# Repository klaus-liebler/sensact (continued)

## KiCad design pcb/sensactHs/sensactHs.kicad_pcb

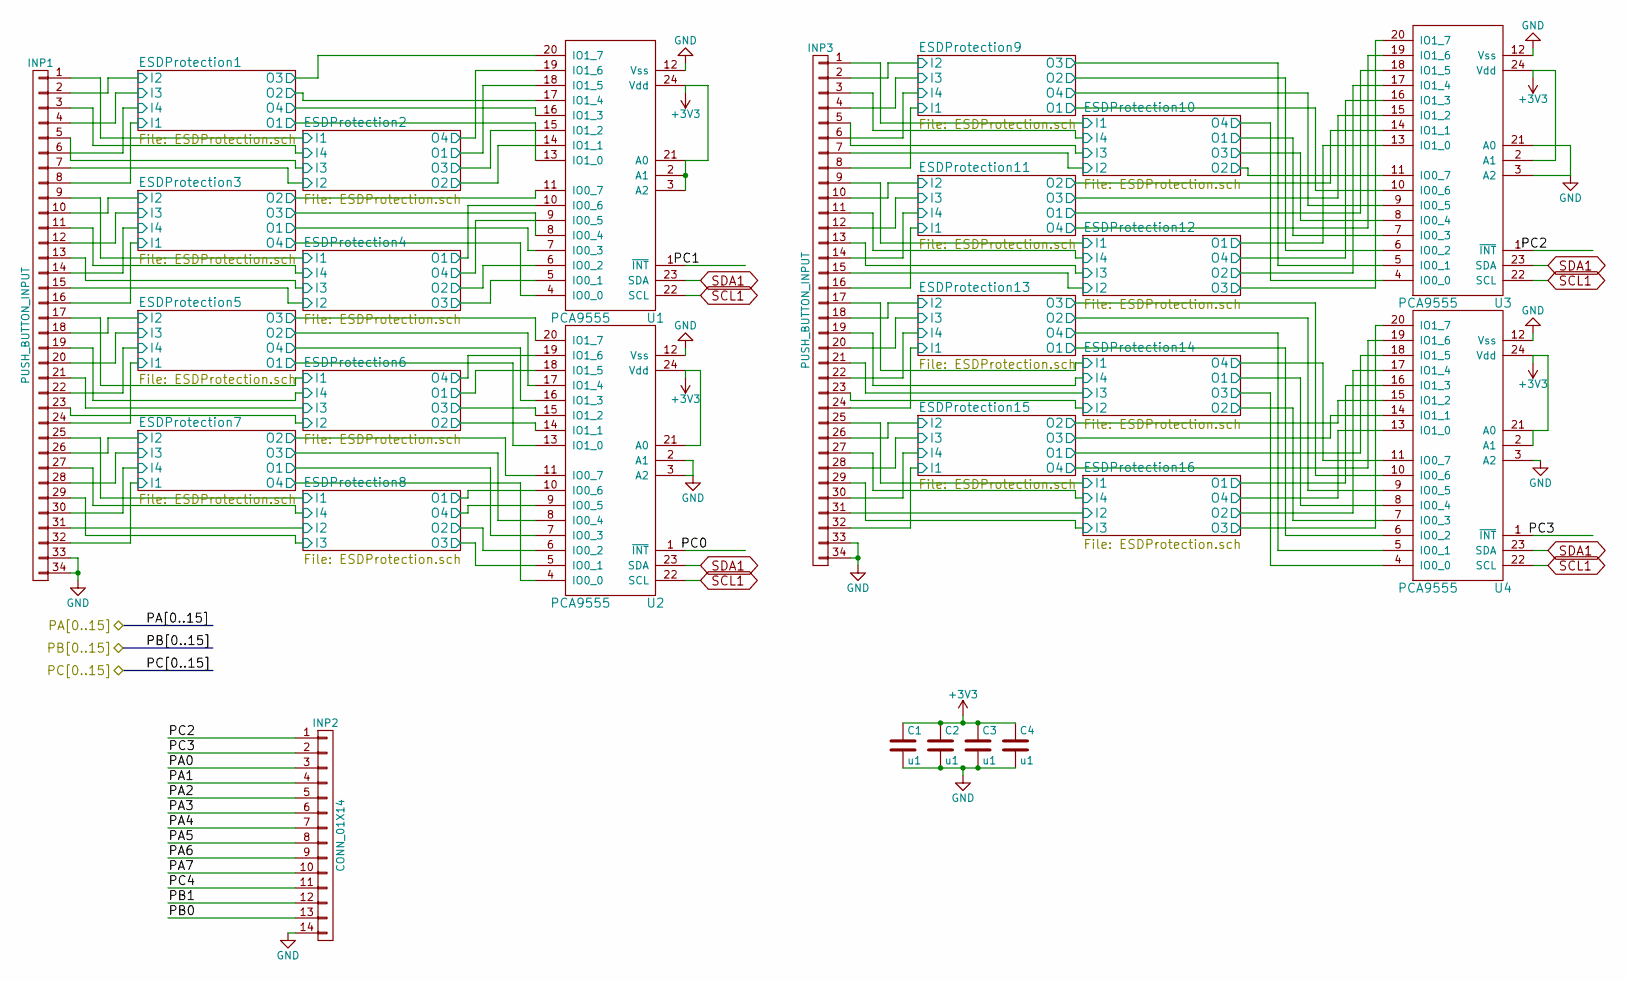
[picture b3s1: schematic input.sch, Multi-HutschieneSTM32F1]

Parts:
C1, C2, C3, C4: u1; C_0805_HandSoldering
INP1, INP3: PUSH_BUTTON_INPUT; vasch_strip_17x2
INP2: CONN_01X14; vasch_strip_7x2
U1, U2, U3, U4: PCA9555; TSSOP-24_4.4x7.8mm_Pitch0.65mm_handsolder

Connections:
/01 input/ESDProtection1/I1: INP1.8; also elsewhere on the board
/01 input/ESDProtection1/I2: INP1.2; also elsewhere on the board
/01 input/ESDProtection1/I3: INP1.4; also elsewhere on the board
/01 input/ESDProtection1/I4: INP1.6; also elsewhere on the board
/01 input/ESDProtection1/O1: U1.13 (IO1_0); also elsewhere on the board
/01 input/ESDProtection1/O2: U1.17 (IO1_4); also elsewhere on the board
/01 input/ESDProtection1/O3: U1.20 (IO1_7); also elsewhere on the board
/01 input/ESDProtection1/O4: U1.16 (IO1_3); also elsewhere on the board
/01 input/ESDProtection2/I1: INP1.1; also elsewhere on the board
/01 input/ESDProtection2/I2: INP1.7; also elsewhere on the board
/01 input/ESDProtection2/I3: INP1.5; also elsewhere on the board
/01 input/ESDProtection2/I4: INP1.3; also elsewhere on the board
/01 input/ESDProtection2/O1: U1.18 (IO1_5); also elsewhere on the board
/01 input/ESDProtection2/O2: U1.14 (IO1_1); also elsewhere on the board
/01 input/ESDProtection2/O3: U1.15 (IO1_2); also elsewhere on the board
/01 input/ESDProtection2/O4: U1.19 (IO1_6); also elsewhere on the board
/01 input/ESDProtection3/I1: INP1.16; also elsewhere on the board
/01 input/ESDProtection3/I2: INP1.10; also elsewhere on the board
/01 input/ESDProtection3/I3: INP1.12; also elsewhere on the board
/01 input/ESDProtection3/I4: INP1.14; also elsewhere on the board
/01 input/ESDProtection3/O1: U1.7 (IO0_3); also elsewhere on the board
/01 input/ESDProtection3/O2: U1.11 (IO0_7); also elsewhere on the board
/01 input/ESDProtection3/O3: U1.8 (IO0_4); also elsewhere on the board
/01 input/ESDProtection3/O4: U1.4 (IO0_0); also elsewhere on the board
/01 input/ESDProtection4/I1: INP1.9; also elsewhere on the board
/01 input/ESDProtection4/I2: INP1.15; also elsewhere on the board
/01 input/ESDProtection4/I3: INP1.13; also elsewhere on the board
/01 input/ESDProtection4/I4: INP1.11; also elsewhere on the board
/01 input/ESDProtection4/O1: U1.10 (IO0_6); also elsewhere on the board
/01 input/ESDProtection4/O2: U1.6 (IO0_2); also elsewhere on the board
/01 input/ESDProtection4/O3: U1.5 (IO0_1); also elsewhere on the board
/01 input/ESDProtection4/O4: U1.9 (IO0_5); also elsewhere on the board
/01 input/ESDProtection5/I1: INP1.24; also elsewhere on the board
/01 input/ESDProtection5/I2: INP1.18; also elsewhere on the board
/01 input/ESDProtection5/I3: INP1.20; also elsewhere on the board
/01 input/ESDProtection5/I4: INP1.22; also elsewhere on the board
/01 input/ESDProtection5/O1: U2.13 (IO1_0); also elsewhere on the board
/01 input/ESDProtection5/O2: U2.17 (IO1_4); also elsewhere on the board
/01 input/ESDProtection5/O3: U2.20 (IO1_7); also elsewhere on the board
/01 input/ESDProtection5/O4: U2.16 (IO1_3); also elsewhere on the board
/01 input/ESDProtection6/I1: INP1.17; also elsewhere on the board
/01 input/ESDProtection6/I2: INP1.23; also elsewhere on the board
/01 input/ESDProtection6/I3: INP1.21; also elsewhere on the board
/01 input/ESDProtection6/I4: INP1.19; also elsewhere on the board
/01 input/ESDProtection6/O1: U2.18 (IO1_5); also elsewhere on the board
/01 input/ESDProtection6/O2: U2.14 (IO1_1); also elsewhere on the board
/01 input/ESDProtection6/O3: U2.15 (IO1_2); also elsewhere on the board
/01 input/ESDProtection6/O4: U2.19 (IO1_6); also elsewhere on the board
/01 input/ESDProtection7/I1: INP1.32; also elsewhere on the board
/01 input/ESDProtection7/I2: INP1.26; also elsewhere on the board
/01 input/ESDProtection7/I3: INP1.28; also elsewhere on the board
/01 input/ESDProtection7/I4: INP1.30; also elsewhere on the board
/01 input/ESDProtection7/O1: U2.7 (IO0_3); also elsewhere on the board
/01 input/ESDProtection7/O2: U2.11 (IO0_7); also elsewhere on the board
/01 input/ESDProtection7/O3: U2.8 (IO0_4); also elsewhere on the board
/01 input/ESDProtection7/O4: U2.4 (IO0_0); also elsewhere on the board
/01 input/ESDProtection8/I1: INP1.25; also elsewhere on the board
/01 input/ESDProtection8/I2: INP1.31; also elsewhere on the board
/01 input/ESDProtection8/I3: INP1.29; also elsewhere on the board
/01 input/ESDProtection8/I4: INP1.27; also elsewhere on the board
/01 input/ESDProtection8/O1: U2.10 (IO0_6); also elsewhere on the board
/01 input/ESDProtection8/O2: U2.6 (IO0_2); also elsewhere on the board
/01 input/ESDProtection8/O3: U2.5 (IO0_1); also elsewhere on the board
/01 input/ESDProtection8/O4: U2.9 (IO0_5); also elsewhere on the board
/01 input/ESDProtection9/I1: INP3.8; also elsewhere on the board
/01 input/ESDProtection9/I2: INP3.2; also elsewhere on the board
/01 input/ESDProtection9/I3: INP3.4; also elsewhere on the board
/01 input/ESDProtection9/I4: INP3.6; also elsewhere on the board
/01 input/ESDProtection9/O1: U3.10 (IO0_6); also elsewhere on the board
/01 input/ESDProtection9/O2: U3.6 (IO0_2); also elsewhere on the board
/01 input/ESDProtection9/O3: U3.5 (IO0_1); also elsewhere on the board
/01 input/ESDProtection9/O4: U3.9 (IO0_5); also elsewhere on the board
/01 input/ESDProtection10/I1: INP3.1; also elsewhere on the board
/01 input/ESDProtection10/I2: INP3.7; also elsewhere on the board
/01 input/ESDProtection10/I3: INP3.5; also elsewhere on the board
/01 input/ESDProtection10/I4: INP3.3; also elsewhere on the board
/01 input/ESDProtection10/O1: U3.7 (IO0_3); also elsewhere on the board
/01 input/ESDProtection10/O2: U3.11 (IO0_7); also elsewhere on the board
/01 input/ESDProtection10/O3: U3.8 (IO0_4); also elsewhere on the board
/01 input/ESDProtection10/O4: U3.4 (IO0_0); also elsewhere on the board
/01 input/ESDProtection11/I1: INP3.16; also elsewhere on the board
/01 input/ESDProtection11/I2: INP3.10; also elsewhere on the board
/01 input/ESDProtection11/I3: INP3.12; also elsewhere on the board
/01 input/ESDProtection11/I4: INP3.14; also elsewhere on the board
/01 input/ESDProtection11/O1: U3.18 (IO1_5); also elsewhere on the board
/01 input/ESDProtection11/O2: U3.14 (IO1_1); also elsewhere on the board
/01 input/ESDProtection11/O3: U3.15 (IO1_2); also elsewhere on the board
/01 input/ESDProtection11/O4: U3.19 (IO1_6); also elsewhere on the board
/01 input/ESDProtection12/I1: INP3.9; also elsewhere on the board
/01 input/ESDProtection12/I2: INP3.15; also elsewhere on the board
/01 input/ESDProtection12/I3: INP3.13; also elsewhere on the board
/01 input/ESDProtection12/I4: INP3.11; also elsewhere on the board
/01 input/ESDProtection12/O1: U3.13 (IO1_0); also elsewhere on the board
/01 input/ESDProtection12/O2: U3.17 (IO1_4); also elsewhere on the board
/01 input/ESDProtection12/O3: U3.20 (IO1_7); also elsewhere on the board
/01 input/ESDProtection12/O4: U3.16 (IO1_3); also elsewhere on the board
/01 input/ESDProtection13/I1: INP3.24; also elsewhere on the board
/01 input/ESDProtection13/I2: INP3.18; also elsewhere on the board
/01 input/ESDProtection13/I3: INP3.20; also elsewhere on the board
/01 input/ESDProtection13/I4: INP3.22; also elsewhere on the board
/01 input/ESDProtection13/O1: U4.6 (IO0_2); also elsewhere on the board
/01 input/ESDProtection13/O2: U4.9 (IO0_5); also elsewhere on the board
/01 input/ESDProtection13/O3: U4.10 (IO0_6); also elsewhere on the board
/01 input/ESDProtection13/O4: U4.5 (IO0_1); also elsewhere on the board
/01 input/ESDProtection14/I1: INP3.17; also elsewhere on the board
/01 input/ESDProtection14/I2: INP3.23; also elsewhere on the board
/01 input/ESDProtection14/I3: INP3.21; also elsewhere on the board
/01 input/ESDProtection14/I4: INP3.19; also elsewhere on the board
/01 input/ESDProtection14/O1: U4.8 (IO0_4); also elsewhere on the board
/01 input/ESDProtection14/O2: U4.7 (IO0_3); also elsewhere on the board
/01 input/ESDProtection14/O3: U4.4 (IO0_0); also elsewhere on the board
/01 input/ESDProtection14/O4: U4.11 (IO0_7); also elsewhere on the board
/01 input/ESDProtection15/I1: INP3.32; also elsewhere on the board
/01 input/ESDProtection15/I2: INP3.26; also elsewhere on the board
/01 input/ESDProtection15/I3: INP3.28; also elsewhere on the board
/01 input/ESDProtection15/I4: INP3.30; also elsewhere on the board
/01 input/ESDProtection15/O1: U4.18 (IO1_5); also elsewhere on the board
/01 input/ESDProtection15/O2: U4.15 (IO1_2); also elsewhere on the board
/01 input/ESDProtection15/O3: U4.14 (IO1_1); also elsewhere on the board
/01 input/ESDProtection15/O4: U4.19 (IO1_6); also elsewhere on the board
/01 input/ESDProtection16/I1: INP3.25; also elsewhere on the board
/01 input/ESDProtection16/I2: INP3.31; also elsewhere on the board
/01 input/ESDProtection16/I3: INP3.29; also elsewhere on the board
/01 input/ESDProtection16/I4: INP3.27; also elsewhere on the board
/01 input/ESDProtection16/O1: U4.16 (IO1_3); also elsewhere on the board
/01 input/ESDProtection16/O2: U4.17 (IO1_4); also elsewhere on the board
/01 input/ESDProtection16/O3: U4.20 (IO1_7); also elsewhere on the board
/01 input/ESDProtection16/O4: U4.13 (IO1_0); also elsewhere on the board
/01 input/PA0: INP2.3; also elsewhere on the board
/01 input/PA1: INP2.4; also elsewhere on the board
/01 input/PA2: INP2.5; also elsewhere on the board
/01 input/PA3: INP2.13; also elsewhere on the board
/01 input/PA4: INP2.11; also elsewhere on the board
/01 input/PA5: INP2.12; also elsewhere on the board
/01 input/PA6: INP2.9; also elsewhere on the board
/01 input/PA7: INP2.10; also elsewhere on the board
/01 input/PB0: INP2.8; also elsewhere on the board
/01 input/PC0: U2.1 (~INT); also elsewhere on the board
/01 input/PC1: U1.1 (~INT); also elsewhere on the board
/01 input/PC4: INP2.7; also elsewhere on the board
/PB1: INP2.6; also elsewhere on the board
GND: C1.2, C2.2, C3.2, C4.2, INP1.33, INP1.34, INP2.14, INP3.33, INP3.34, U1.12 (Vss), U2.2 (A1), U2.3 (A2), U2.12 (Vss), U3.3 (A2), U3.12 (Vss), U3.21 (A0), U4.3 (A2), U4.12 (Vss); also elsewhere on the board
SCL1: U1.22 (SCL), U2.22 (SCL), U3.22 (SCL), U4.22 (SCL); also elsewhere on the board
SDA1: U1.23 (SDA), U2.23 (SDA), U3.23 (SDA), U4.23 (SDA); also elsewhere on the board

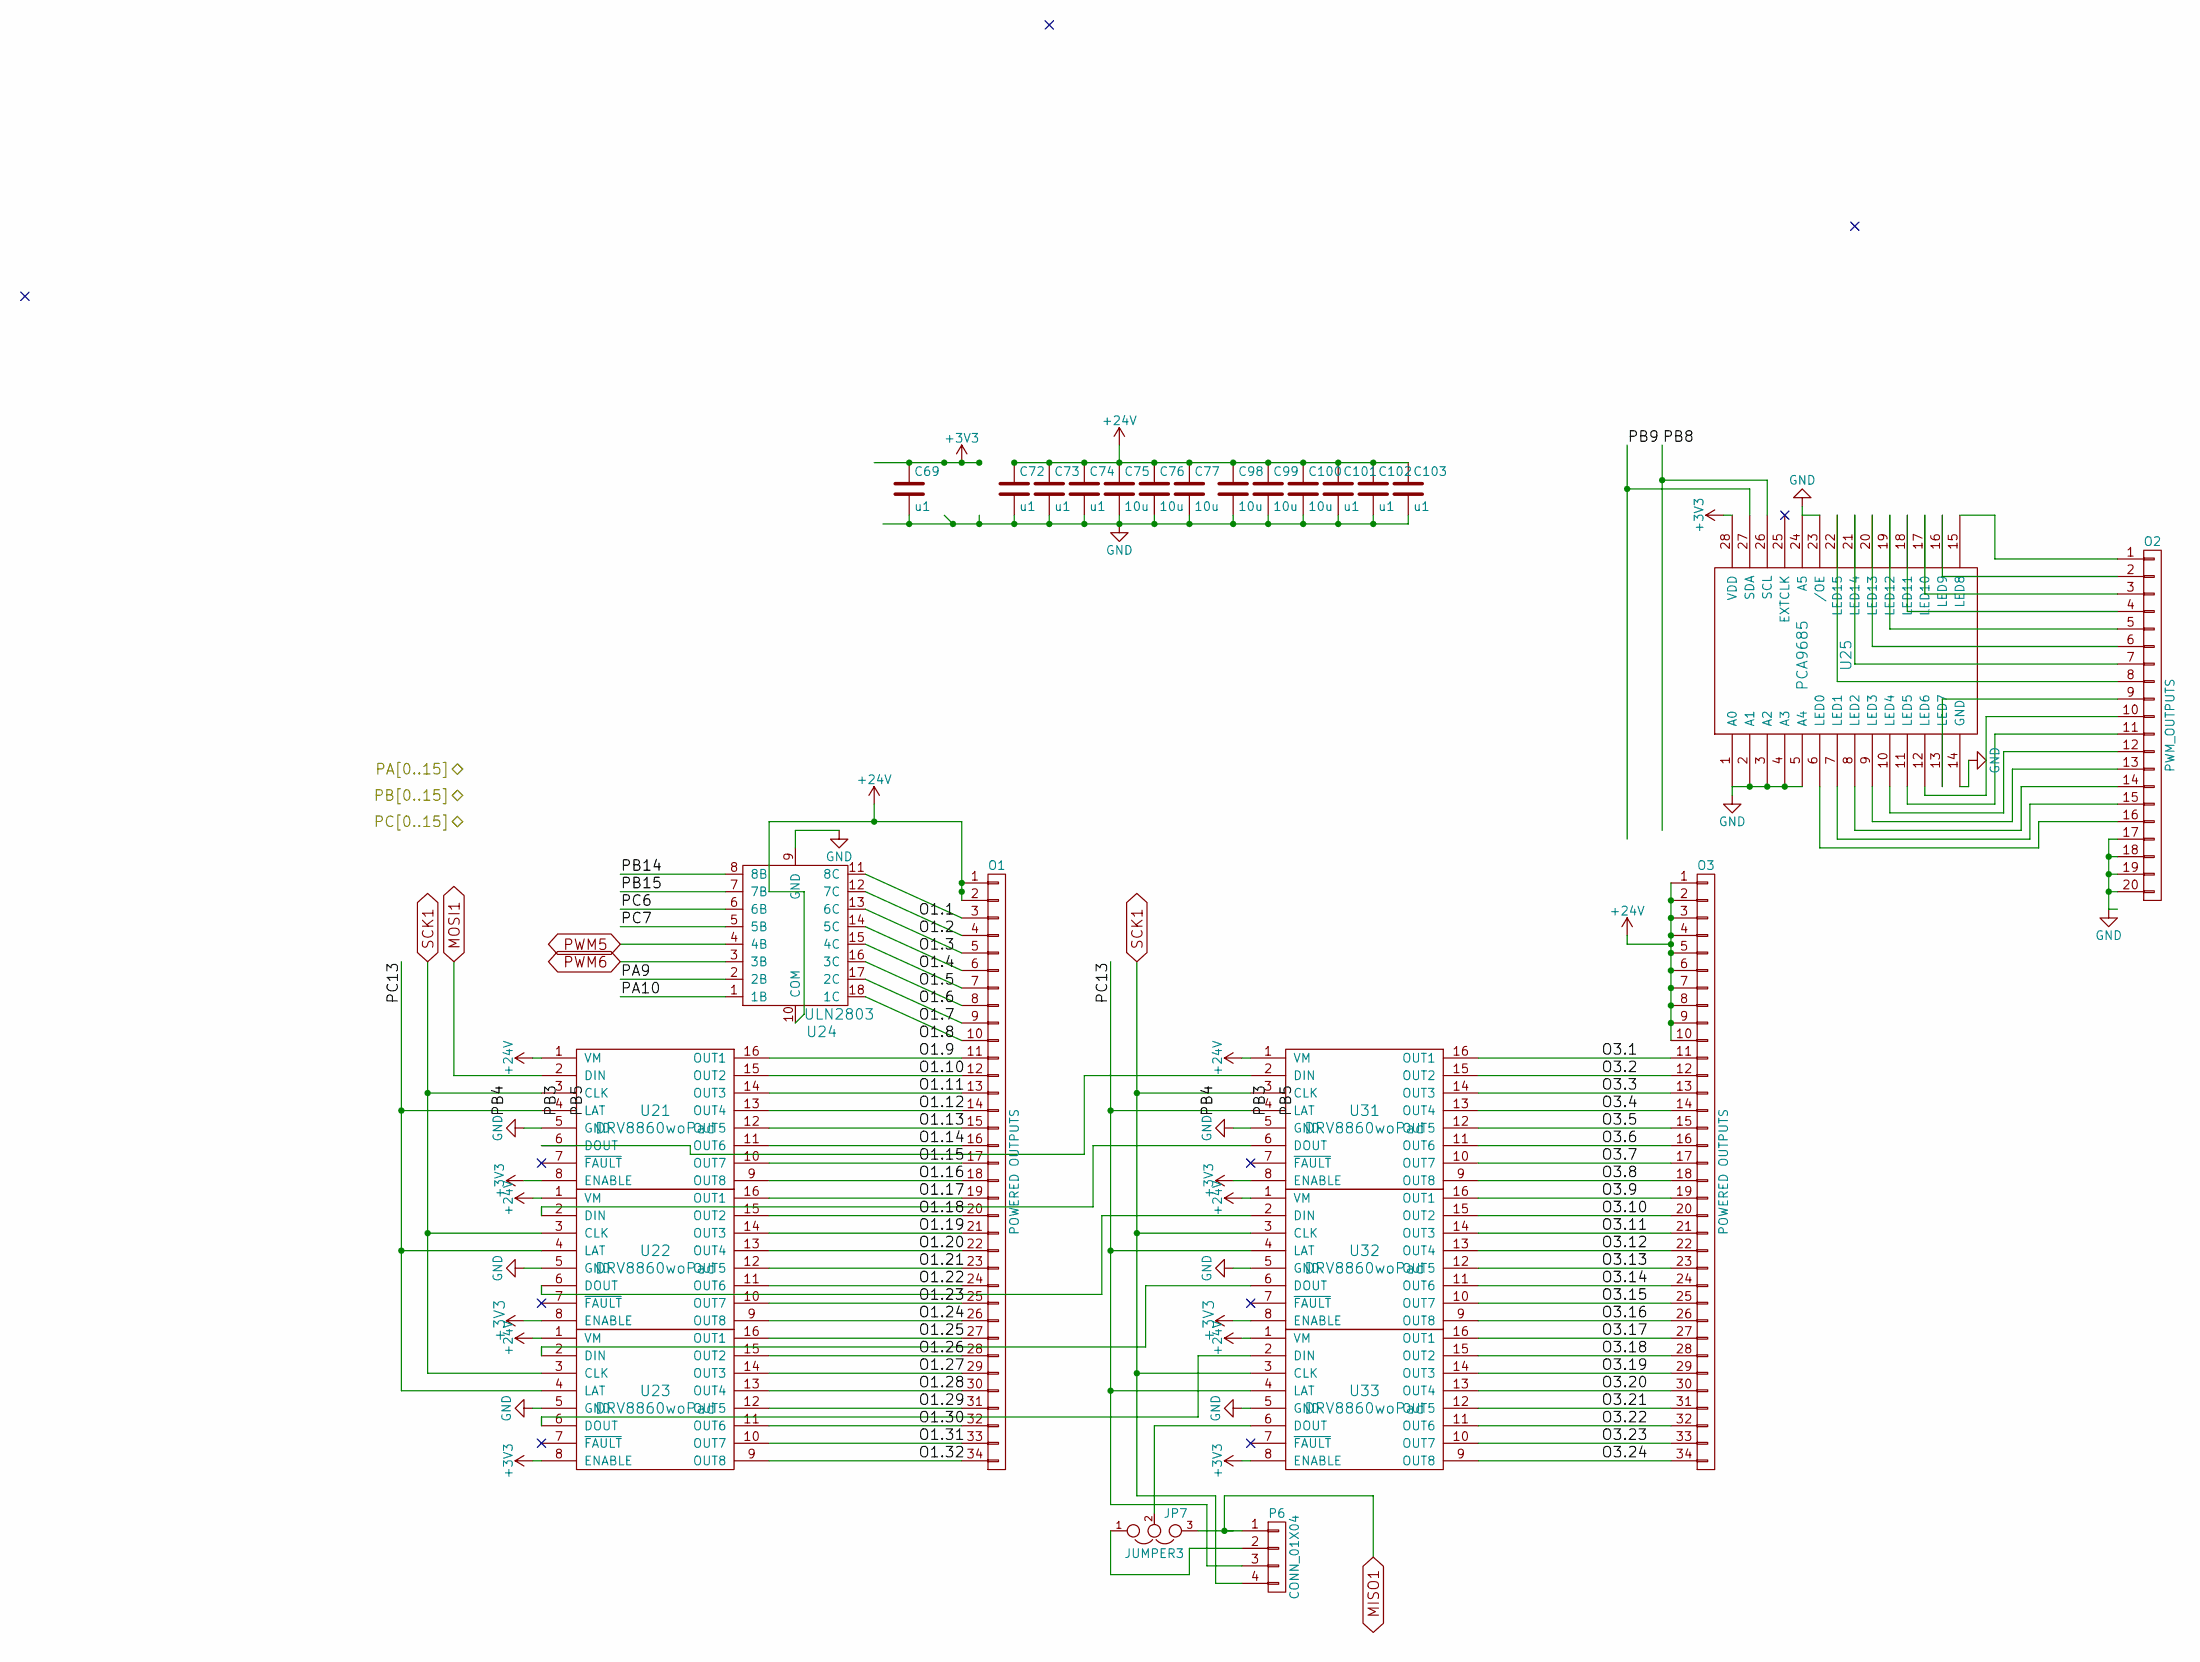
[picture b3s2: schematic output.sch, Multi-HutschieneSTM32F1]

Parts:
C69, C72, C73, C74, C101, C102, C103: u1; C_0805_HandSoldering
C75, C76, C77, C98, C99, C100: 10u; C_1206_HandSoldering
JP7: JUMPER3; SMD-solder-bridge-3pin
O1, O3: POWERED OUTPUTS; vasch_strip_17x2
O2: PWM_OUTPUTS; vasch_strip_10x2
P6: CONN_01X04; Pin_Header_Straight_2x02
U21, U22, U23, U31, U32, U33: DRV8860woPad; TSSOP-16_4.4x5mm_Pitch0.65mm_handsolder
U24: ULN2803; SOIC-18_7.5x11.6mm_Pitch1.27mm_handsolder
U25: PCA9685; TSSOP-28_4.4x9.7mm_Pitch0.65mm_handsolder

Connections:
+24V: C72.1, C73.1, C74.1, C75.1, C76.1, C77.1, C98.1, C99.1, C100.1, C101.1, C102.1, C103.1, O1.1, O1.2, O3.1, O3.2, O3.3, O3.4, O3.5, O3.6, O3.7, O3.8, O3.9, O3.10, U21.1 (VM), U22.1 (VM), U23.1 (VM), U24.10 (COM), U31.1 (VM), U32.1 (VM), U33.1 (VM); also elsewhere on the board
/02 output/O1.9: O1.11, U21.16 (OUT1)
/02 output/O1.10: O1.12, U21.15 (OUT2)
/02 output/O1.11: O1.13, U21.14 (OUT3)
/02 output/O1.12: O1.14, U21.13 (OUT4)
/02 output/O1.13: O1.15, U21.12 (OUT5)
/02 output/O1.14: O1.16, U21.11 (OUT6)
/02 output/O1.15: O1.17, U21.10 (OUT7)
/02 output/O1.16: O1.18, U21.9 (OUT8)
/02 output/O1.17: O1.19, U22.16 (OUT1)
/02 output/O1.18: O1.20, U22.15 (OUT2)
/02 output/O1.19: O1.21, U22.14 (OUT3)
/02 output/O1.20: O1.22, U22.13 (OUT4)
/02 output/O1.21: O1.23, U22.12 (OUT5)
/02 output/O1.22: O1.24, U22.11 (OUT6)
/02 output/O1.23: O1.25, U22.10 (OUT7)
/02 output/O1.24: O1.26, U22.9 (OUT8)
/02 output/O1.25: O1.27, U23.16 (OUT1)
/02 output/O1.26: O1.28, U23.15 (OUT2)
/02 output/O1.27: O1.29, U23.14 (OUT3)
/02 output/O1.28: O1.30, U23.13 (OUT4)
/02 output/O1.29: O1.31, U23.12 (OUT5)
/02 output/O1.30: O1.32, U23.11 (OUT6)
/02 output/O1.31: O1.33, U23.10 (OUT7)
/02 output/O1.32: O1.34, U23.9 (OUT8)
/02 output/O3.1: O3.11, U31.16 (OUT1)
/02 output/O3.2: O3.12, U31.15 (OUT2)
/02 output/O3.3: O3.13, U31.14 (OUT3)
/02 output/O3.4: O3.14, U31.13 (OUT4)
/02 output/O3.5: O3.15, U31.12 (OUT5)
/02 output/O3.6: O3.16, U31.11 (OUT6)
/02 output/O3.7: O3.17, U31.10 (OUT7)
/02 output/O3.8: O3.18, U31.9 (OUT8)
/02 output/O3.9: O3.19, U32.16 (OUT1)
/02 output/O3.10: O3.20, U32.15 (OUT2)
/02 output/O3.11: O3.21, U32.14 (OUT3)
/02 output/O3.12: O3.22, U32.13 (OUT4)
/02 output/O3.13: O3.23, U32.12 (OUT5)
/02 output/O3.14: O3.24, U32.11 (OUT6)
/02 output/O3.15: O3.25, U32.10 (OUT7)
/02 output/O3.16: O3.26, U32.9 (OUT8)
/02 output/O3.17: O3.27, U33.16 (OUT1)
/02 output/O3.18: O3.28, U33.15 (OUT2)
/02 output/O3.19: O3.29, U33.14 (OUT3)
/02 output/O3.20: O3.30, U33.13 (OUT4)
/02 output/O3.21: O3.31, U33.12 (OUT5)
/02 output/O3.22: O3.32, U33.11 (OUT6)
/02 output/O3.23: O3.33, U33.10 (OUT7)
/02 output/O3.24: O3.34, U33.9 (OUT8)
/02 output/PA9: U24.2 (2B); also elsewhere on the board
/02 output/PA10: U24.1 (1B); also elsewhere on the board
/02 output/PB14: U24.8 (8B); also elsewhere on the board
/02 output/PB15: U24.7 (7B); also elsewhere on the board
/02 output/PC6: U24.6 (6B); also elsewhere on the board
/02 output/PC7: U24.5 (5B); also elsewhere on the board
GND: C69.2, C72.2, C73.2, C74.2, C75.2, C76.2, C77.2, C98.2, C99.2, C100.2, C101.2, C102.2, C103.2, O2.17, O2.18, O2.19, O2.20, U21.5 (GND), U22.5 (GND), U23.5 (GND), U24.9 (GND), U25.1 (A0), U25.2 (A1), U25.3 (A2), U25.4 (A3), U25.5 (A4), U25.14 (GND), U25.23 (/OE), U25.24 (A5), U31.5 (GND), U32.5 (GND), U33.5 (GND); also elsewhere on the board
MOSI1: U21.2 (DIN); also elsewhere on the board
unnamed: O1.3, U24.11 (8C)
unnamed: O1.4, U24.12 (7C)
unnamed: O1.5, U24.13 (6C)
unnamed: O1.6, U24.14 (5C)
unnamed: O1.7, U24.15 (4C)
unnamed: O1.8, U24.16 (3C)
unnamed: O1.9, U24.17 (2C)
unnamed: O1.10, U24.18 (1C)
unnamed: O2.1, U25.15 (LED8)
unnamed: O2.2, U25.16 (LED9)
unnamed: O2.3, U25.17 (LED10)
unnamed: O2.4, U25.18 (LED11)
unnamed: O2.5, U25.19 (LED12)
unnamed: O2.6, U25.20 (LED13)
unnamed: O2.7, U25.21 (LED14)
unnamed: O2.8, U25.22 (LED15)
unnamed: O2.9, U25.13 (LED7)
unnamed: O2.10, U25.12 (LED6)
unnamed: O2.11, U25.11 (LED5)
unnamed: O2.12, U25.10 (LED4)
unnamed: O2.13, U25.9 (LED3)
unnamed: O2.14, U25.8 (LED2)
unnamed: O2.15, U25.7 (LED1)
unnamed: O2.16, U25.6 (LED0)
unnamed: U21.6 (DOUT), U31.2 (DIN)
unnamed: U22.2 (DIN), U31.6 (DOUT)
unnamed: U22.6 (DOUT), U32.2 (DIN)
unnamed: U23.2 (DIN), U32.6 (DOUT)
unnamed: U23.6 (DOUT), U33.2 (DIN)
PWM5: U24.4 (4B); also elsewhere on the board
PWM6: U24.3 (3B); also elsewhere on the board
SCL1: U25.26 (SCL); also elsewhere on the board
SDA1: U25.27 (SDA); also elsewhere on the board

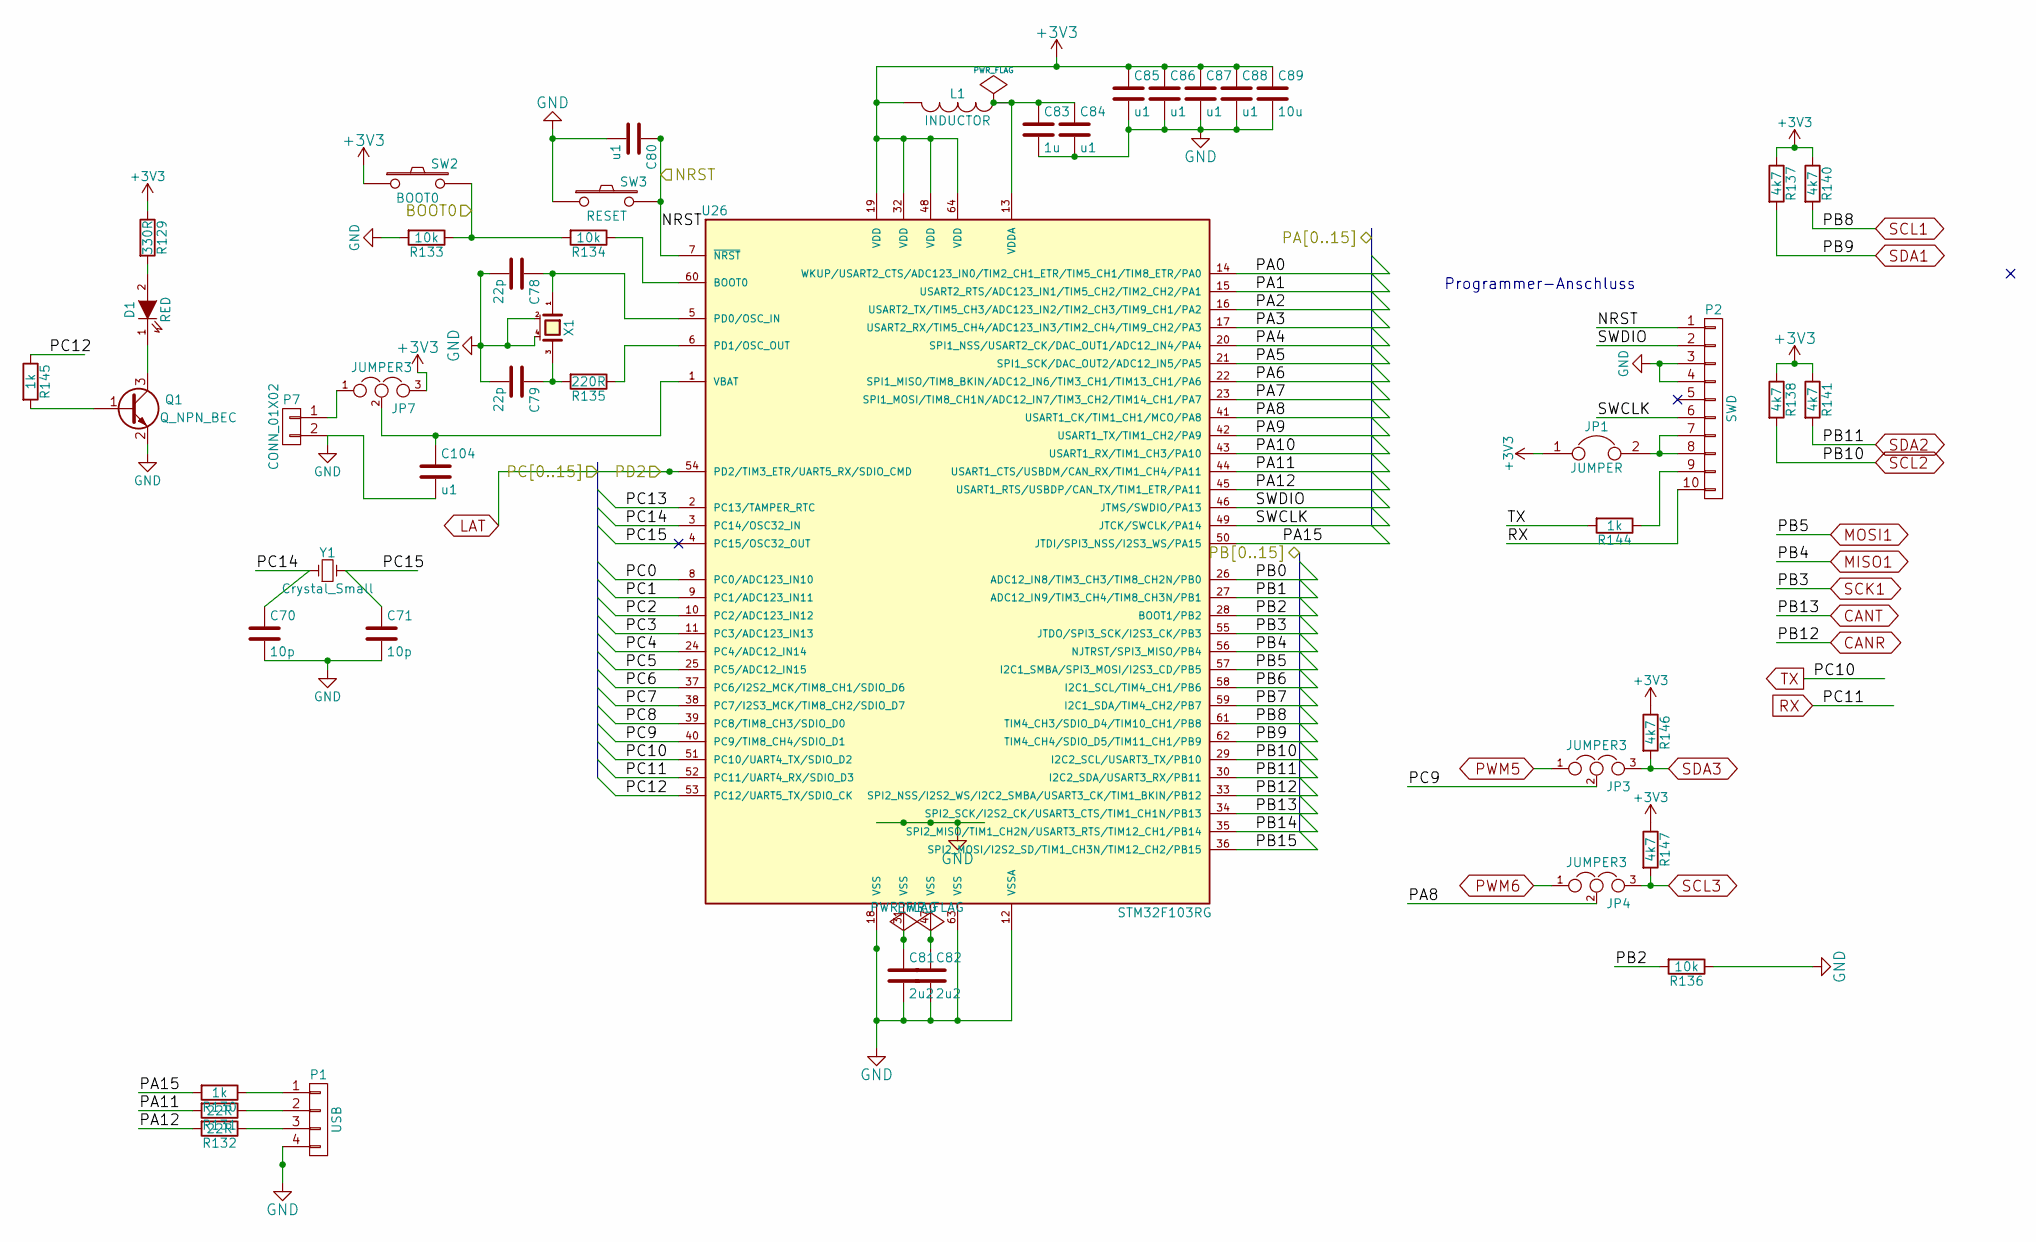
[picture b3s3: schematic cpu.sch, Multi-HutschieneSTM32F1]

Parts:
C70, C71: 10p; C_0805_HandSoldering
C78, C79: 22p; C_0805_HandSoldering
C80, C84, C85, C86, C87, C88, C104: u1; C_0805_HandSoldering
C81, C82: 2u2; C_0805_HandSoldering
C83: 1u; C_0805_HandSoldering
C89: 10u; C_1206_HandSoldering
D1: RED; LED_5730
JP1: JUMPER; Pin_Header_Straight_1x02
JP3, JP4, JP7: JUMPER3; SMD-solder-bridge-3pin
L1: INDUCTOR; R_1206_HandSoldering
P1: USB; Pin_Header_Straight_1x04
P2: SWD; vasch_strip_5x2
P7: CONN_01X02; Pin_Header_Straight_1x02
Q1: Q_NPN_BEC; SOT-23_Handsoldering
R129: 330R; R_1206_HandSoldering
R130, R144, R145: 1k; R_0805_HandSoldering
R131, R132: 22R; R_0805_HandSoldering
R133, R134, R136: 10k; R_0805_HandSoldering
R135: 220R; R_0805_HandSoldering
R137, R138, R140, R141, R146, R147: 4k7; R_0805_HandSoldering
SW2: BOOT0; SW_PUSH_SMALL
SW3: RESET; SW_PUSH_SMALL
U26: STM32F103RG; LQFP-64_10x10mm_Pitch0.5mm_handsolder
X1: CRYSTAL_SMD_4pol; quartz3225
Y1: Crystal_Small; Crystal_Watch

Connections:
/01 input/PA0: U26.14 (WKUP/USART2_CTS/ADC123_IN0/TIM2_CH1_ETR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); also elsewhere on the board
/01 input/PA1: U26.15 (USART2_RTS/ADC123_IN1/TIM5_CH2/TIM2_CH2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); also elsewhere on the board
/01 input/PA2: U26.16 (USART2_TX/TIM5_CH3/ADC123_IN2/TIM2_CH3/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); also elsewhere on the board
/01 input/PA3: U26.17 (USART2_RX/TIM5_CH4/ADC123_IN3/TIM2_CH4/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); also elsewhere on the board
/01 input/PA4: U26.20 (SPI1_NSS/USART2_CK/DAC_OUT1/ADC12_IN4/P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); also elsewhere on the board
/01 input/PA5: U26.21 (SPI1_SCK/DAC_OUT2/ADC12_IN5/PA5); also elsewhere on the board
/01 input/PA6: U26.22 (SPI1_MISO/TIM8_BKIN/ADC12_IN6/TIM3_CH1/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); also elsewhere on the board
/01 input/PA7: U26.23 (SPI1_MOSI/TIM8_CH1N/ADC12_IN7/TIM3_CH2/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); also elsewhere on the board
/01 input/PB0: U26.26 (ADC12_IN8/TIM3_CH3/TIM8_CH2N/PB0); also elsewhere on the board
/01 input/PC0: U26.8 (PC0/ADC123_IN10); also elsewhere on the board
/01 input/PC1: U26.9 (PC1/ADC123_IN11); also elsewhere on the board
/01 input/PC4: U26.24 (PC4/ADC12_IN14); also elsewhere on the board
/02 output/PA9: U26.42 (USART1_TX/TIM1_CH2/PA9); also elsewhere on the board
/02 output/PA10: U26.43 (USART1_RX/TIM1_CH3/PA10); also elsewhere on the board
/02 output/PB14: U26.35 (SPI2_MISO/TIM1_CH2N/USART3_RTS/TIM12_CH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); also elsewhere on the board
/02 output/PB15: U26.36 (SPI2_MOSI/I2S2_SD/TIM1_CH3N/TIM12_CH2/P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); also elsewhere on the board
/02 output/PC6: U26.37 (PC6/I2S2_MCK/TIM8_CH1/SDIO_D6); also elsewhere on the board
/02 output/PC7: U26.38 (PC7/I2S3_MCK/TIM8_CH2/SDIO_D7); also elsewhere on the board
/03 cpu/PA8: JP4.2, U26.41 (USART1_CK/TIM1_CH1/MCO/PA8)
/03 cpu/PA11: R131.2, U26.44 (USART1_CTS/USBDM/CAN_RX/TIM1_CH4/PA11)
/03 cpu/PA12: R132.2, U26.45 (USART1_RTS/USBDP/CAN_TX/TIM1_ETR/PA11)
/03 cpu/PA15: R130.2, U26.50 (JTDI/SPI3_NSS/I2S3_WS/PA15)
/03 cpu/PB2: R136.2, U26.28 (BOOT1/PB2)
/03 cpu/PC9: JP3.2, U26.40 (PC9/TIM8_CH4/SDIO_D1)
/03 cpu/PC12: R145.1, U26.53 (PC12/UART5_TX/SDIO_CK)
/03 cpu/PC14: C70.1, U26.3 (PC14/OSC32_IN), Y1.1
/03 cpu/PC15: C71.1, U26.4 (PC15/OSC32_OUT), Y1.2
/03 cpu/SWCLK: P2.6, U26.49 (JTCK/SWCLK/PA14)
/03 cpu/SWDIO: P2.2, U26.46 (JTMS/SWDIO/PA13)
/BOOT0: R133.1, R134.2, SW2.2
/NRST: C80.1, P2.1, SW3.2, U26.7 (~NRST)
/PB1: U26.27 (ADC12_IN9/TIM3_CH4/TIM8_CH3N/PB1); also elsewhere on the board
CANR: U26.33 (SPI2_NSS/I2S2_WS/I2C2_SMBA/USART3_CK/TI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); also elsewhere on the board
CANT: U26.34 (SPI2_SCK/I2S2_CK/USART3_CTS/TIM1_CH1N/P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); also elsewhere on the board
GND: C70.2, C71.2, C78.2, C79.2, C80.2, C81.2, C82.2, C83.2, C84.2, C85.2, C86.2, C87.2, C88.2, C89.2, C104.2, P1.4, P2.3, P2.4, P7.2, Q1.2 (E), R133.2, R136.1, SW3.1, U26.12 (VSSA), U26.18 (VSS), U26.63 (VSS), X1.2 (case), X1.4 (case); also elsewhere on the board
MOSI1: U26.57 (I2C1_SMBA/SPI3_MOSI/I2S3_CD/PB5); also elsewhere on the board
unnamed: C78.1, U26.5 (PD0/OSC_IN), X1.1
unnamed: C79.1, R135.2, X1.3
unnamed: C81.1, U26.31 (VSS)
unnamed: C82.1, U26.47 (VSS)
unnamed: C83.1, C84.1, L1.1, U26.13 (VDDA)
unnamed: D1.1 (K), Q1.3 (C)
unnamed: D1.2 (A), R129.2
unnamed: JP1.2, P2.7, P2.8
unnamed: P1.1, R130.1
unnamed: P1.2, R131.1
unnamed: P1.3, R132.1
unnamed: P2.9, R144.1
unnamed: Q1.1 (B), R145.2
unnamed: R134.1, U26.60 (BOOT0)
unnamed: R135.1, U26.6 (PD1/OSC_OUT)
PWM5: JP3.1; also elsewhere on the board
PWM6: JP4.1; also elsewhere on the board
RX: P2.10, U26.52 (PC11/UART4_RX/SDIO_D3)
SCL1: R140.2, U26.61 (TIM4_CH3/SDIO_D4/TIM10_CH1/PB8); also elsewhere on the board
SCL2: R138.2, U26.29 (I2C2_SCL/USART3_TX/PB10); also elsewhere on the board
SCL3: JP4.3, R147.2; also elsewhere on the board
SDA1: R137.2, U26.62 (TIM4_CH4/SDIO_D5/TIM11_CH1/PB9); also elsewhere on the board
SDA2: R141.2, U26.30 (I2C2_SDA/USART3_RX/PB11); also elsewhere on the board
SDA3: JP3.3, R146.2; also elsewhere on the board
TX: R144.2, U26.51 (PC10/UART4_TX/SDIO_D2)

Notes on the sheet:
Programmer-Anschluss

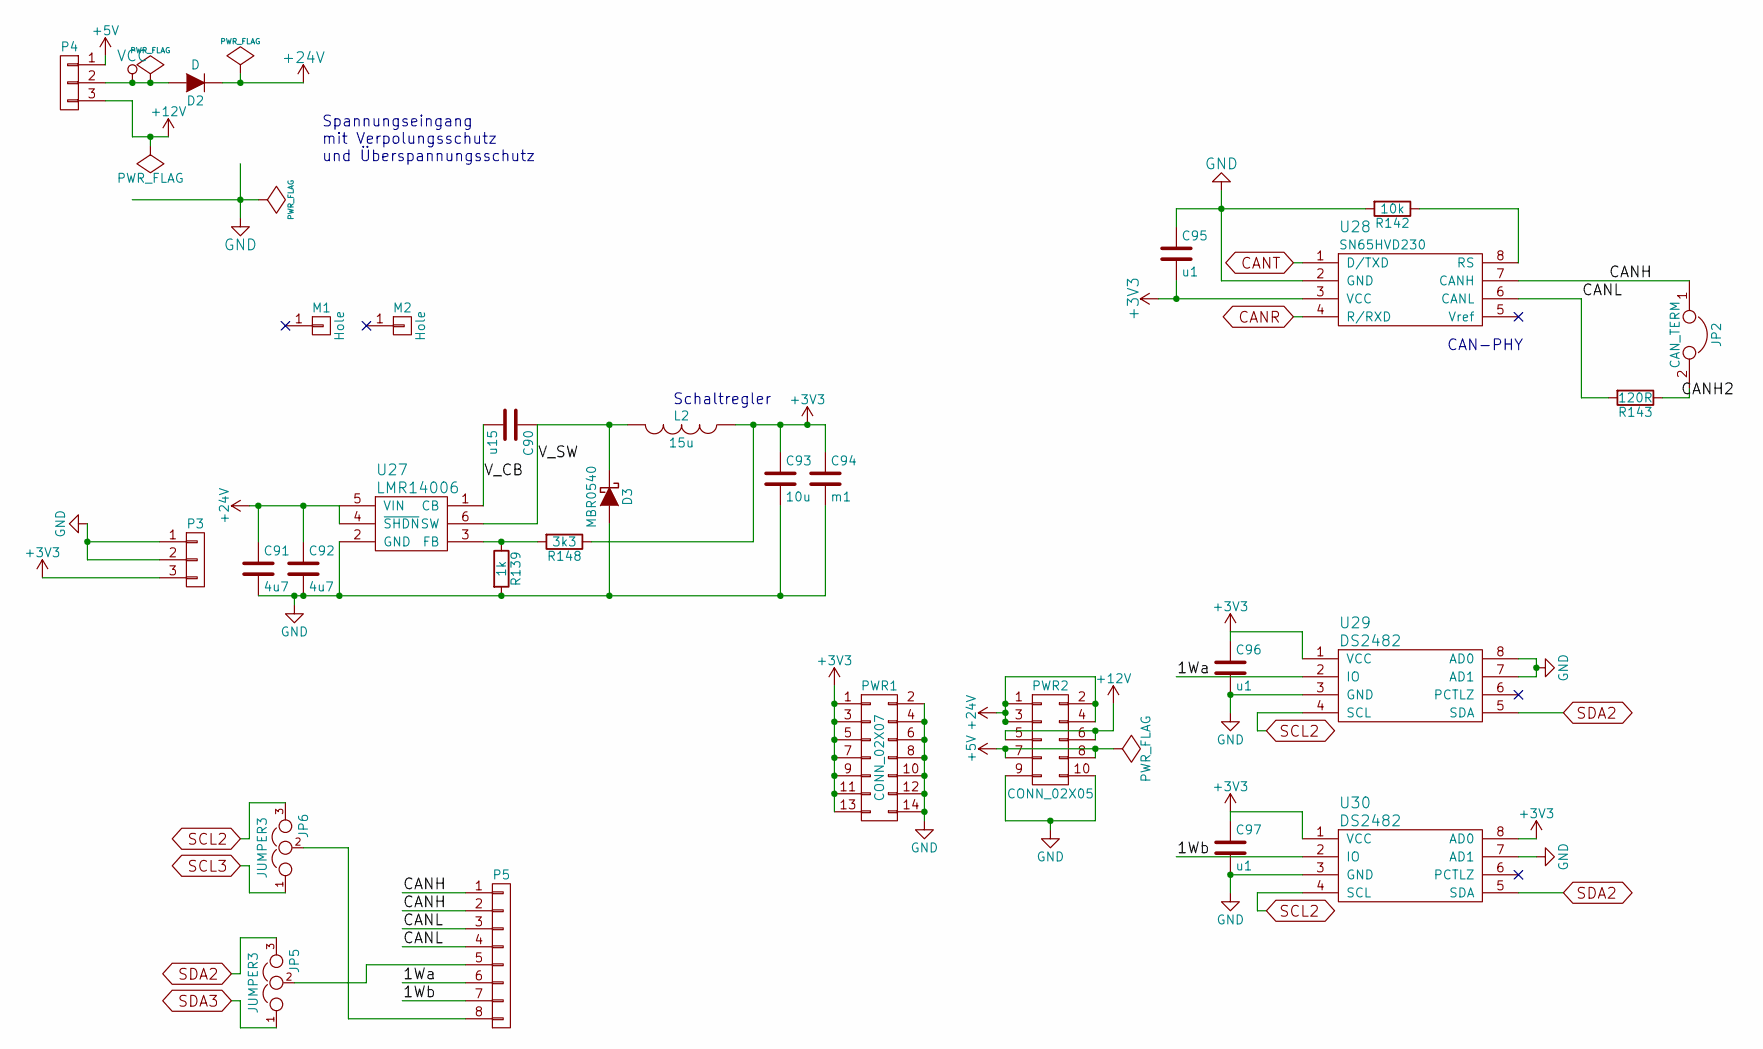
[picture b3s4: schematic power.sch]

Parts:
C90: u15; C_0805_HandSoldering
C91, C92: 4u7; C_1206_HandSoldering
C93: 10u; C_1206_HandSoldering
C94: m1; C_1206_HandSoldering
C95, C96, C97: u1; C_0805_HandSoldering
D2: D; do214ac_handsolder
D3: MBR0540; do214ac_handsolder
JP2: CAN_TERM; Pin_Header_Straight_1x02
JP5, JP6: JUMPER3; SMD-solder-bridge-3pin
L2: 15u; CD54
M1, M2: Hole; MountingHole_3mm
P3: 2; KF141R-3p
P4: 1; KF141R-3p
P5: 3; KF141R-8p
PWR1: CONN_02X07; vasch_strip_7x2
PWR2: CONN_02X05; vasch_strip_5x2
R139: 1k; R_0805_HandSoldering
R142: 10k; R_0805_HandSoldering
R143: 120R; R_1206_HandSoldering
R148: 3k3; R_0805_HandSoldering
U27: LMR14006; SOT-23-6_handsolder
U28: SN65HVD230; SOIC-8_3.9x4.9mm_Pitch1.27mm_handsolder
U29, U30: DS2482; SOIC-8_3.9x4.9mm_Pitch1.27mm_handsolder

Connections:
+5V: P4.1, PWR2.7, PWR2.8
+12V: P4.3, PWR2.5, PWR2.6
+24V: C91.1, C92.1, D2.1 (K), PWR2.1, PWR2.2, PWR2.3, PWR2.4, U27.4 (~SHDN), U27.5 (VIN); also elsewhere on the board
/04 power/1Wa: P5.6, U29.2 (IO)
/04 power/1Wb: P5.7, U30.2 (IO)
/04 power/CANH: JP2.1, P5.1, P5.2, U28.7 (CANH)
/04 power/CANH2: JP2.2, R143.1
/04 power/CANL: P5.3, P5.4, R143.2, U28.6 (CANL)
/04 power/V_CB: C90.2, U27.1 (CB)
/04 power/V_SW: C90.1, D3.1 (K), L2.2, U27.6 (SW)
CANR: U28.4 (R/RXD); also elsewhere on the board
CANT: U28.1 (D/TXD); also elsewhere on the board
GND: C91.2, C92.2, C93.2, C94.2, C95.1, C96.2, C97.2, D3.2 (A), P3.1, P3.2, PWR1.2, PWR1.4, PWR1.6, PWR1.8, PWR1.10, PWR1.12, PWR1.14, PWR2.9, PWR2.10, R139.2, R142.2, U27.2 (GND), U28.2 (GND), U29.3 (GND), U29.7 (AD1), U29.8 (AD0), U30.3 (GND), U30.7 (AD1); also elsewhere on the board
unnamed: JP5.2, P5.5
unnamed: JP6.2, P5.8
unnamed: R139.1, R148.2, U27.3 (FB)
unnamed: R142.1, U28.8 (RS)
SCL2: JP6.3, U29.4 (SCL), U30.4 (SCL); also elsewhere on the board
SCL3: JP6.1; also elsewhere on the board
SDA2: JP5.3, U29.5 (SDA), U30.5 (SDA); also elsewhere on the board
SDA3: JP5.1; also elsewhere on the board
VCC: D2.2 (A), P4.2

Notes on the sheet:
Spannungseingang mit Verpolungsschutz und Überspannungsschutz
Schaltregler
CAN-PHY
